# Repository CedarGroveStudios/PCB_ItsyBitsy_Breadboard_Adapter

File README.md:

### _A stacking breadboard adapter for the ItsyBitsy M4 Express_

# ItsyBitsy Breadboard Adapter

## Overview
The ItsyBitsy Breadboard Adapter is an Adafruit ItsyBitsy M4 Express-compatible piggyback module that converts the 3-sided pinout of the ItsyBitsy to dual in-line for use on typical solderless breadboards and soldered protoboards. The adapter was also designed with extra solderable pin connections and mounting ears for permanent installation.

Included is a STEMMA-QT connector that can be optionally configured via solder jumpers to connect to the ItsyBitsy's UART (RX/TX) or I2C (SCL/SDA) signals. A 2-pin JST LiPo battery connection is on-board that supports charging (100mA charge rate), compatible with Adafruit's standard battery connector polarity. A solder jumper is also provided to optionally connect the battery monitor voltage divider to pin A6.

ItsyBitsy Breadboard Adapter [Schematic](https://github.com/CedarGroveStudios/PCB_ItsyBitsy_Breadboard_Adapter/blob/main/PCB/ItsyBitsy%20breadboard.pdf)

OSH Park shared project: <a href="https://oshpark.com/shared_projects/f0OLeXN8"></img></a>

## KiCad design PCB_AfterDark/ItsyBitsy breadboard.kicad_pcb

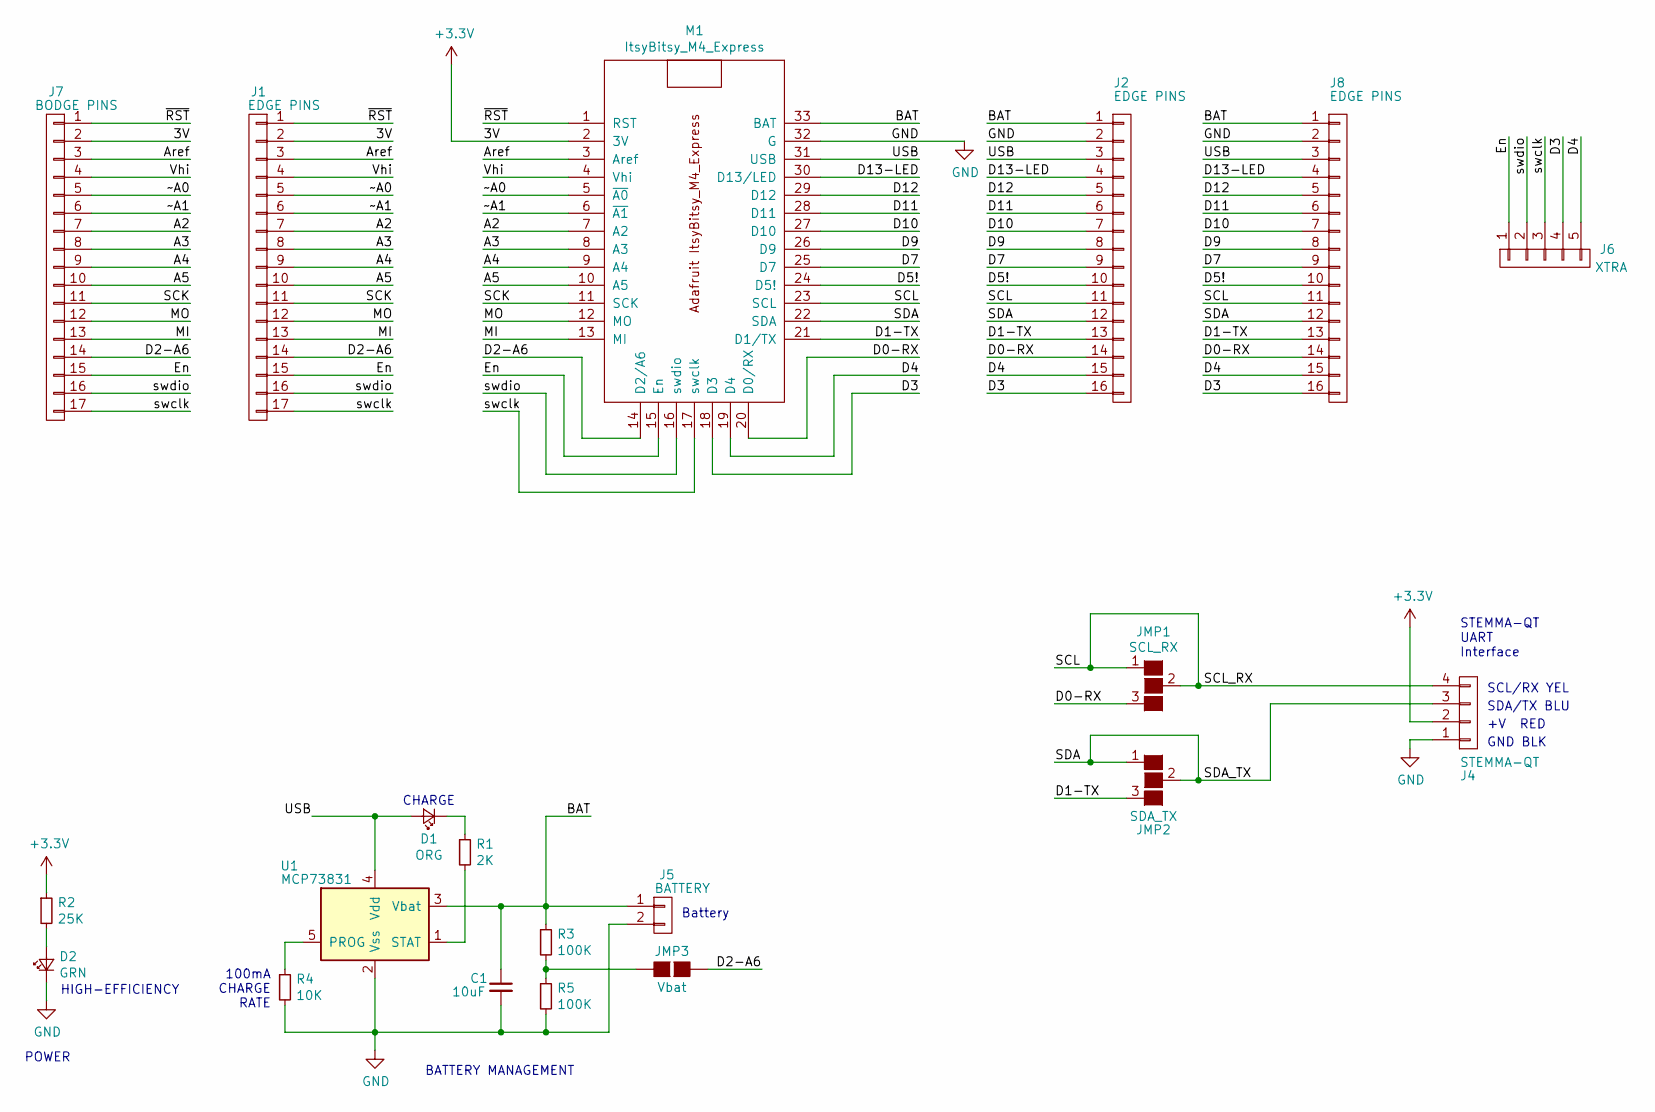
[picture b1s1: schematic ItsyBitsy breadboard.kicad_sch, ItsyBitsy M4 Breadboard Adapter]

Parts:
C1: 10uF; C_0805_2012Metric
D1: ORG; LED_0805_2012Metric
D2: GRN; LED_0805_2012Metric
J1: EDGE PINS; Pin_Header_Straight_1x17_Pitch2.54mm_no_silk
J2, J8: EDGE PINS; Pin_Header_Straight_1x16_Pitch2.54mm_no_silk
J4: STEMMA-QT; JST_SH_SM04B-SRSS-TB_1x04-1MP_P1.00mm_Horizontal
J5: BATTERY; JST_PH_B2B-PH-K_1x02_P2.00mm_Vertical
J6: XTRA; Pin_Header_Straight_1x05_Pitch2.54mm_no_silk
J7: BODGE PINS; Pin_Header_Straight_1x17_Pitch2.54mm_no_silk
JMP1: SCL_RX; GS3
JMP2: SDA_TX; GS3
JMP3: Vbat; GS2
M1: ItsyBitsy_M4_Express
R1: 2K; R_0805_2012Metric
R2: 25K; R_0805_2012Metric
R3, R5: 100K; R_0805_2012Metric
R4: 10K; R_0805_2012Metric
U1: MCP73831; SOT-23-5

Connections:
+3V3: J1.2, J4.2, J7.2, M1.2 (3V), R2.1
/A2: J1.7, J7.7, M1.7 (A2)
/A3: J1.8, J7.8, M1.8 (A3)
/A4: J1.9, J7.9, M1.9 (A4)
/A5: J1.10, J7.10, M1.10 (A5)
/Aref: J1.3, J7.3, M1.3 (Aref)
/BAT: C1.1, J2.1, J5.1, J8.1, M1.33 (BAT), R3.1, U1.3 (Vbat)
/D0-RX: J2.14, J8.14, JMP1.3 (G3), M1.20 (D0/RX)
/D1-TX: J2.13, J8.13, JMP2.3 (G3), M1.21 (D1/TX)
/D2-A6: J1.14, J7.14, JMP3.1 (G1), M1.14 (D2/A6)
/D3: J2.16, J6.4, J8.16, M1.18 (D3)
/D4: J2.15, J6.5, J8.15, M1.19 (D4)
/D5!: J2.10, J8.10, M1.24 (D5!)
/D7: J2.9, J8.9, M1.25 (D7)
/D9: J2.8, J8.8, M1.26 (D9)
/D10: J2.7, J8.7, M1.27 (D10)
/D11: J2.6, J8.6, M1.28 (D11)
/D12: J2.5, J8.5, M1.29 (D12)
/D13-LED: J2.4, J8.4, M1.30 (D13/LED)
/En: J1.15, J6.1, J7.15, M1.15 (En)
/MI: J1.13, J7.13, M1.13 (MI)
/MO: J1.12, J7.12, M1.12 (MO)
/SCK: J1.11, J7.11, M1.11 (SCK)
/SCL: J2.11, J4.4, J8.11, JMP1.1 (G1), JMP1.2 (G2), M1.23 (SCL)
/SDA: J2.12, J4.3, J8.12, JMP2.1 (G1), JMP2.2 (G2), M1.22 (SDA)
/USB: D1.2 (A), J2.3, J8.3, M1.31 (USB), U1.4 (Vdd)
/Vhi: J1.4, J7.4, M1.4 (Vhi)
/swclk: J1.17, J6.3, J7.17, M1.17 (swclk)
/swdio: J1.16, J6.2, J7.16, M1.16 (swdio)
/~A0: J1.5, J7.5, M1.5 (~A0)
/~A1: J1.6, J7.6, M1.6 (~A1)
/~RST: J1.1, J7.1, M1.1 (RST)
GND: C1.2, D2.1 (K), J2.2, J4.1, J5.2, J8.2, M1.32 (G), R4.2, R5.2, U1.2 (Vss)
unnamed: D1.1 (K), R1.1
unnamed: D2.2 (A), R2.2
unnamed: JMP3.2 (G2), R3.2, R5.1
unnamed: R1.2, U1.1 (STAT)
unnamed: R4.1, U1.5 (PROG)

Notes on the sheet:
BATTERY MANAGEMENT
GND BLK
SDA/TX BLU
CHARGE
SCL/RX YEL
Battery
HIGH-EFFICIENCY
STEMMA-QT UART Interface
+V RED
POWER
100mA CHARGE RATE

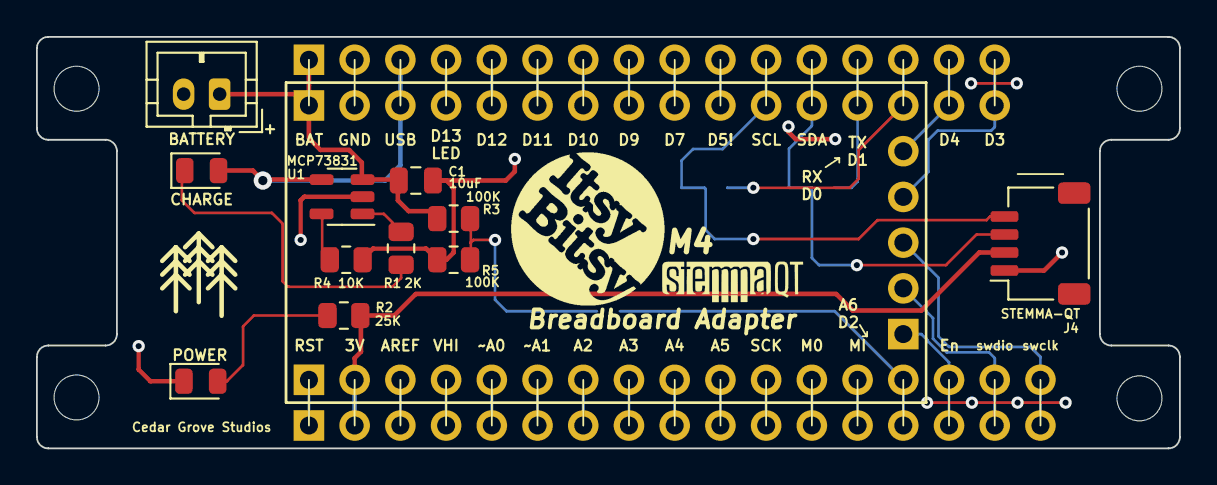
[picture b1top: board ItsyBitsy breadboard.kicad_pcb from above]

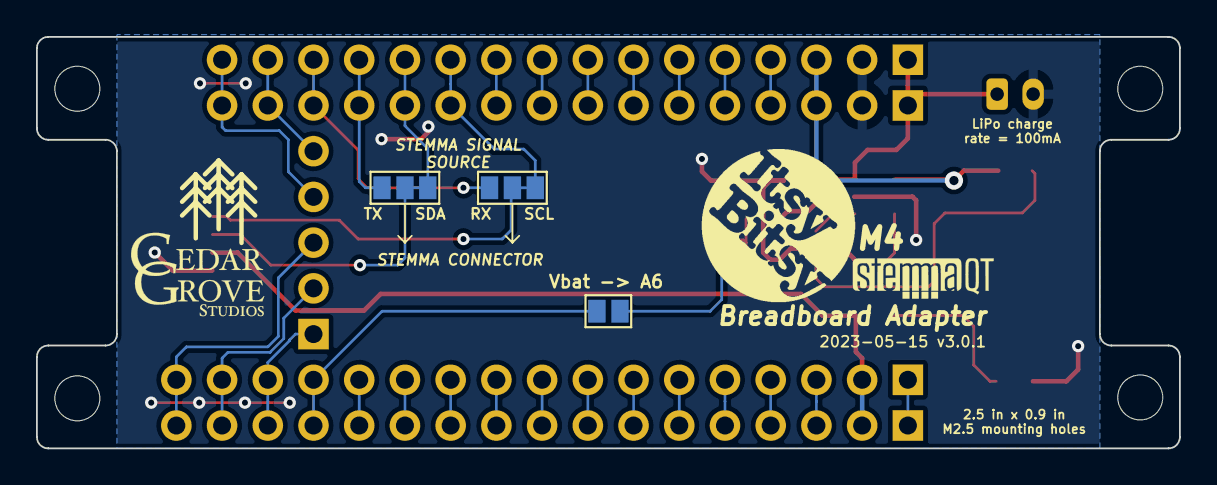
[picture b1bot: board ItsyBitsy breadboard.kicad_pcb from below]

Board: 2 copper layers, 63.5 x 22.9 mm, 21 parts (4 on the bottom side), 38 nets.

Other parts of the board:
logo: ItsyBitsy_logo
logo#2: ItsyBitsy_logo

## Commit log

2023-05-31 initial repo load
2023-06-02 update kicad backups
